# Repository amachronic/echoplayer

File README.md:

# NOTICE

Development has moved to [SourceHut](https://sr.ht/~aidanm/echoplayer).

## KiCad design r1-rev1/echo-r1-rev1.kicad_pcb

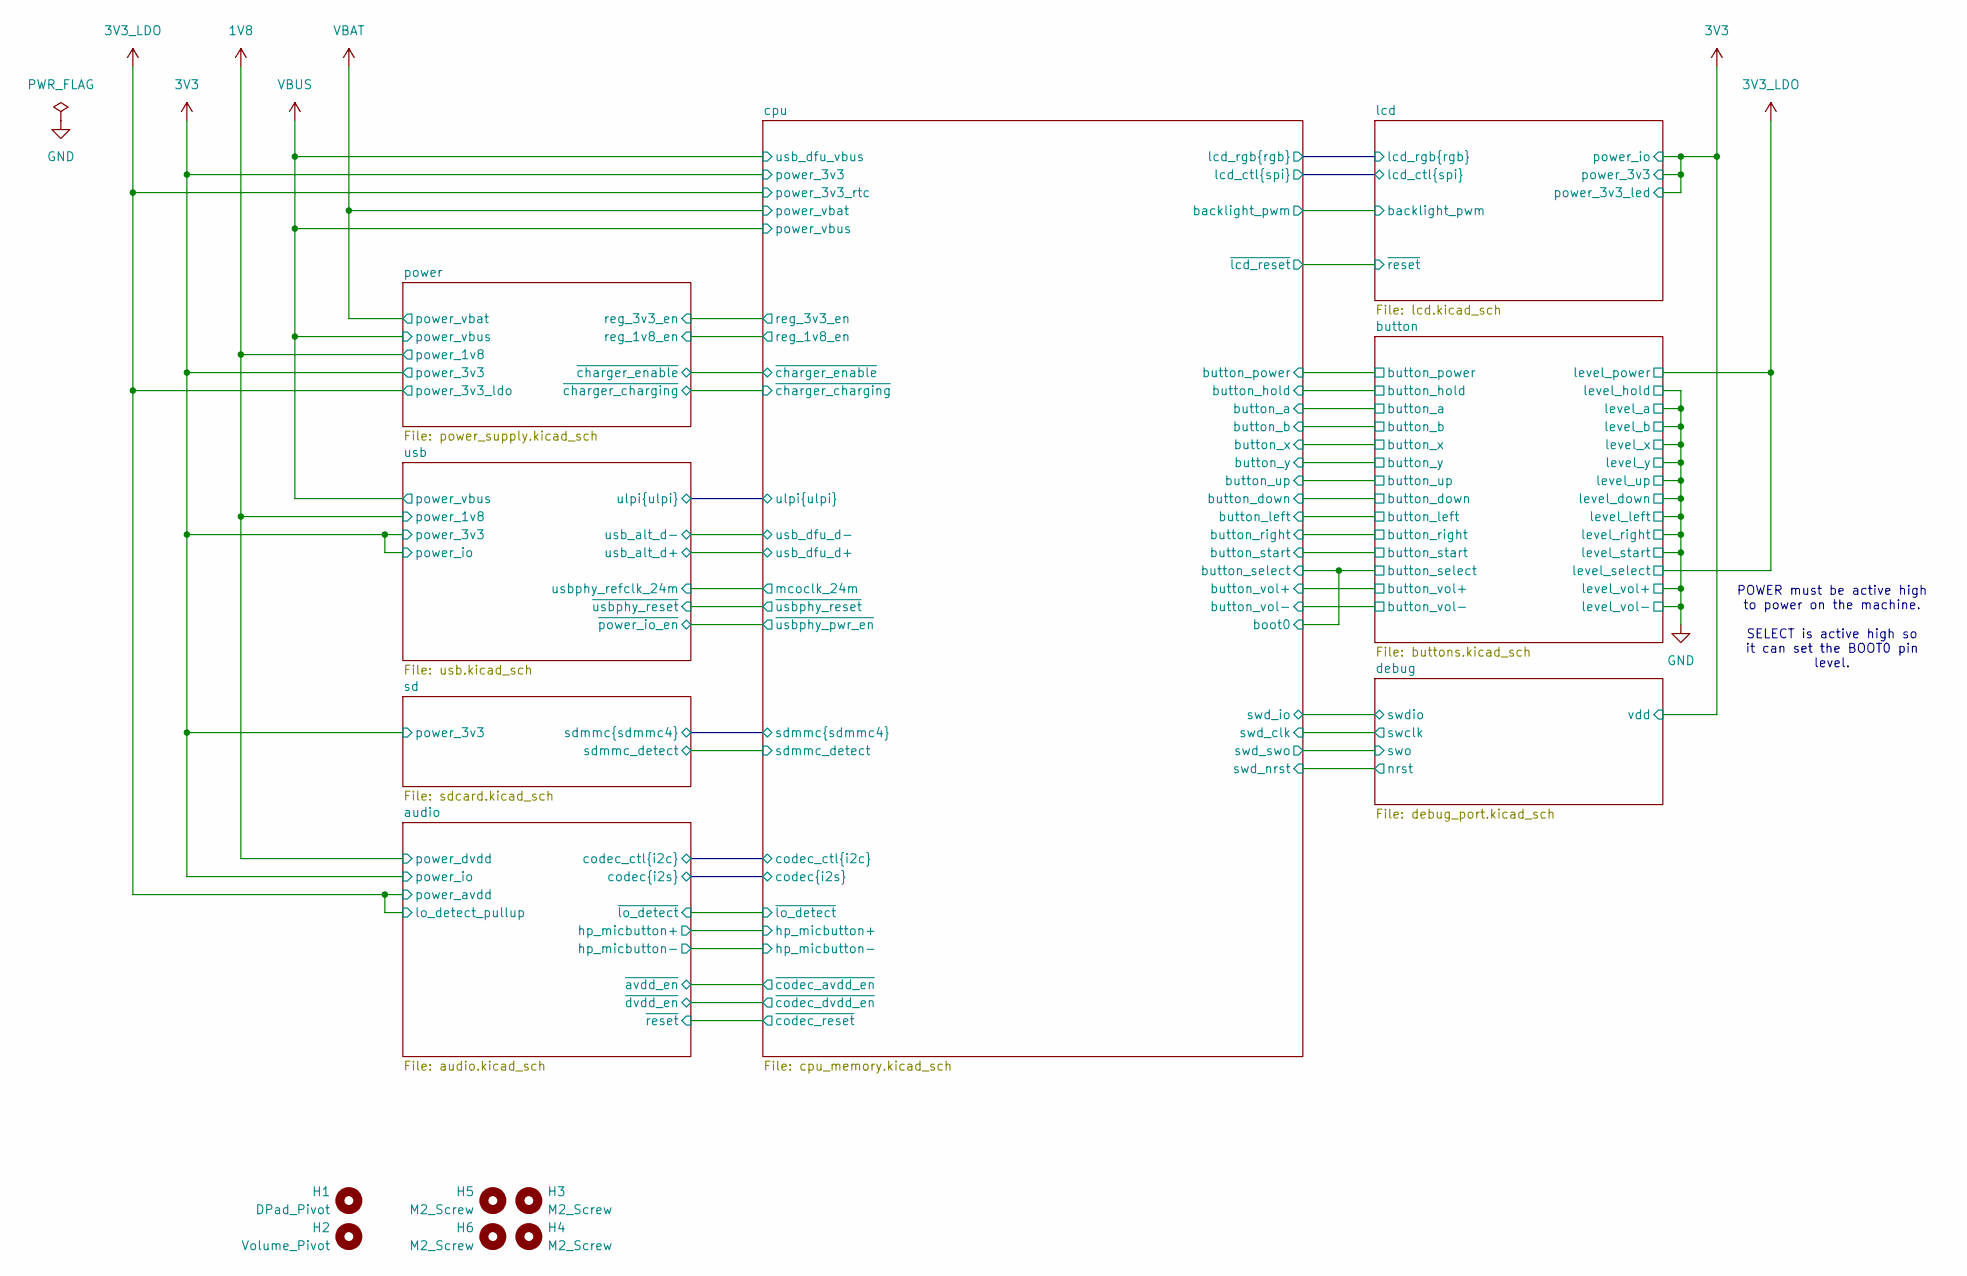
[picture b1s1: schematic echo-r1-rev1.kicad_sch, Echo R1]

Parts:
H1: DPad_Pivot; MountingHole_4mm
H2: Volume_Pivot; MountingHole_4mm
H3, H4, H5, H6: M2_Screw; MountingHole_2.2mm_M2

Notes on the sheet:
POWER must be active high to power on the machine. SELECT is active high so it can set the BOOT0 pin level.

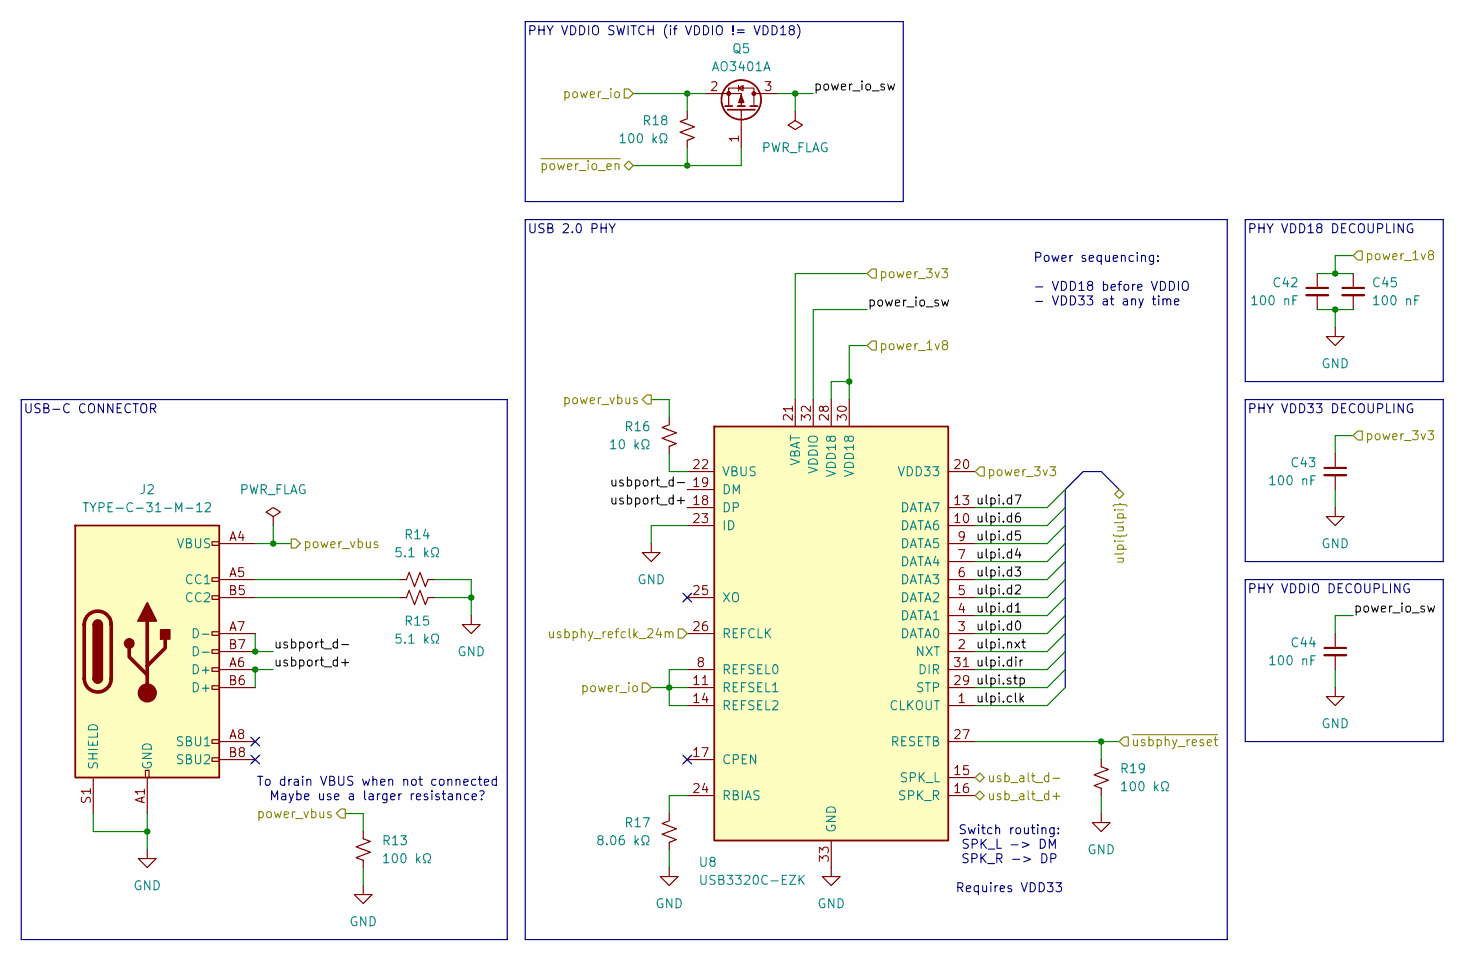
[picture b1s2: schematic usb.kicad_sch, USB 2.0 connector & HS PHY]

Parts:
C42, C43, C44, C45: 100 nF; C_0402_1005Metric; LCSC# C77020
J2: TYPE-C-31-M-12; USB_C-Hroparts-TYPE-C-31-M-12; LCSC# C165948
Q5: AO3401A; SOT-23; LCSC# C347476
R13, R18, R19: 100 kΩ; R_0402_1005Metric; LCSC# C60491
R14, R15: 5.1 kΩ; R_0402_1005Metric; LCSC# C25905
R16: 10 kΩ; R_0402_1005Metric; LCSC# C60490
R17: 8.06 kΩ; R_0402_1005Metric; LCSC# C276278
U8: USB3320C-EZK; QFN-32-1EP_5x5mm_P0.5mm_EP3.1x3.1mm_ThermalVias; LCSC# C132156

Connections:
1V8: C42.1, C45.1, U8.28 (VDD18), U8.30 (VDD18); also elsewhere on the board
3V3: C43.1, Q5.2 (S), R18.1, U8.8 (REFSEL0), U8.11 (REFSEL1), U8.14 (REFSEL2), U8.20 (VDD33), U8.21 (VBAT); also elsewhere on the board
/cpu/mcoclk_24m: U8.26 (REFCLK); also elsewhere on the board
/cpu/ulpi.clk: U8.1 (CLKOUT); also elsewhere on the board
/cpu/ulpi.d0: U8.3 (DATA0); also elsewhere on the board
/cpu/ulpi.d1: U8.4 (DATA1); also elsewhere on the board
/cpu/ulpi.d2: U8.5 (DATA2); also elsewhere on the board
/cpu/ulpi.d3: U8.6 (DATA3); also elsewhere on the board
/cpu/ulpi.d4: U8.7 (DATA4); also elsewhere on the board
/cpu/ulpi.d5: U8.9 (DATA5); also elsewhere on the board
/cpu/ulpi.d6: U8.10 (DATA6); also elsewhere on the board
/cpu/ulpi.d7: U8.13 (DATA7); also elsewhere on the board
/cpu/ulpi.dir: U8.31 (DIR); also elsewhere on the board
/cpu/ulpi.nxt: U8.2 (NXT); also elsewhere on the board
/cpu/ulpi.stp: U8.29 (STP); also elsewhere on the board
/cpu/usb_dfu_d+: U8.16 (SPK_R); also elsewhere on the board
/cpu/usb_dfu_d-: U8.15 (SPK_L); also elsewhere on the board
/cpu/~usbphy_pwr_en: Q5.1 (G), R18.2; also elsewhere on the board
/cpu/~usbphy_reset: R19.1, U8.27 (RESETB); also elsewhere on the board
/usb/power_io_sw: C44.1, Q5.3 (D), U8.32 (VDDIO)
/usb/usbport_d+: J2.A6 (D+), J2.B6 (D+), U8.18 (DP)
/usb/usbport_d-: J2.A7 (D-), J2.B7 (D-), U8.19 (DM)
GND: C42.2, C43.2, C44.2, C45.2, J2.A1 (GND), J2.A12 (GND), J2.B1 (GND), J2.B12 (GND), J2.S1 (SHIELD), R13.2, R14.2, R15.2, R17.1, R19.2, U8.23 (ID), U8.33 (GND); also elsewhere on the board
unnamed: J2.A5 (CC1), R14.1
unnamed: J2.B5 (CC2), R15.1
unnamed: R17.2, U8.24 (RBIAS)
unnamed: R16.1, U8.22 (VBUS)
VBUS: J2.A4 (VBUS), J2.A9 (VBUS), J2.B4 (VBUS), J2.B9 (VBUS), R13.1, R16.2; also elsewhere on the board

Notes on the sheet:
USB 2.0 PHY
Switch routing: SPK_L -> DM SPK_R -> DP Requires VDD33
To drain VBUS when not connected Maybe use a larger resistance?
USB-C CONNECTOR
PHY VDDIO DECOUPLING
PHY VDD33 DECOUPLING
PHY VDD18 DECOUPLING
Power sequencing: - VDD18 before VDDIO - VDD33 at any time
PHY VDDIO SWITCH (if VDDIO != VDD18)

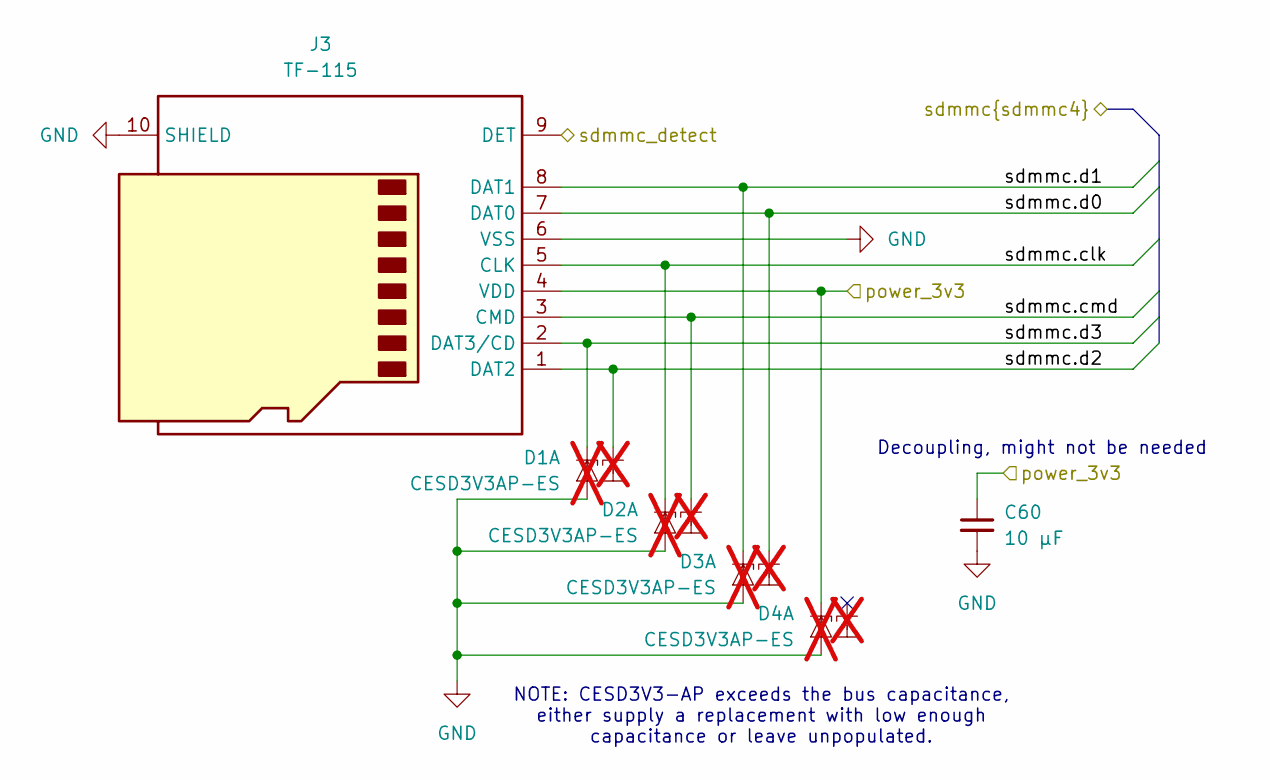
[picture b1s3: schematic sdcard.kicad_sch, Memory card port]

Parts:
C60: 10 µF; C_0603_1608Metric; LCSC# C91606
D1, D2, D3, D4: CESD3V3AP-ES; SOT-23; LCSC# C5199223; not fitted
J3: TF-115; microSD_XUNPU_TF-115; LCSC# C720505

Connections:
3V3: C60.1, D4.1 (K1), J3.4 (VDD); also elsewhere on the board
/cpu/sdmmc.clk: D2.1 (K1), J3.5 (CLK); also elsewhere on the board
/cpu/sdmmc.cmd: D2.2 (K2), J3.3 (CMD); also elsewhere on the board
/cpu/sdmmc.d0: D3.2 (K2), J3.7 (DAT0); also elsewhere on the board
/cpu/sdmmc.d1: D3.1 (K1), J3.8 (DAT1); also elsewhere on the board
/cpu/sdmmc.d2: D1.2 (K2), J3.1 (DAT2); also elsewhere on the board
/cpu/sdmmc.d3: D1.1 (K1), J3.2 (DAT3/CD); also elsewhere on the board
/cpu/sdmmc_detect: J3.9 (DET); also elsewhere on the board
GND: C60.2, D1.3 (A), D2.3 (A), D3.3 (A), D4.3 (A), J3.6 (VSS), J3.10 (SHIELD); also elsewhere on the board

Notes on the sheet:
NOTE: CESD3V3-AP exceeds the bus capacitance, either supply a replacement with low enough capacitance or leave unpopulated.
Decoupling, might not be needed

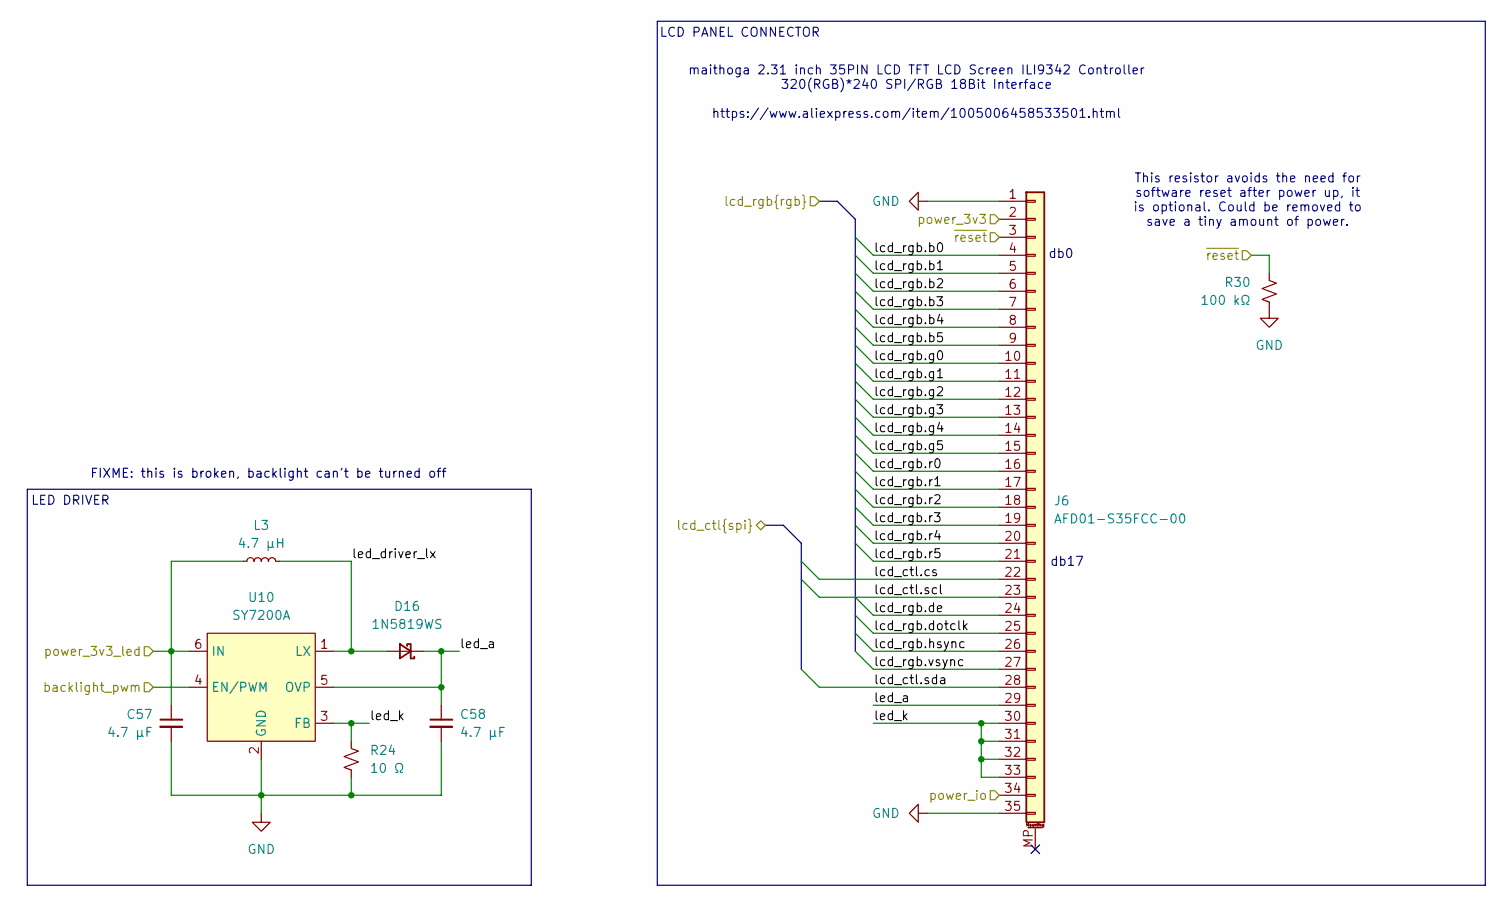
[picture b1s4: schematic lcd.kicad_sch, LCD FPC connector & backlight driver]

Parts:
C57, C58: 4.7 µF; C_0603_1608Metric; LCSC# C69335
D16: 1N5819WS; D_SOD-323; LCSC# C191023
J6: AFD01-S35FCC-00; Conn_Jushuo_AFD01-S35FCC-00_RTL; LCSC# C18198555
L3: 4.7 µH; L_0806_2016Metric; LCSC# C86094
R24: 10 Ω; R_0402_1005Metric; LCSC# C25077
R30: 100 kΩ; R_0402_1005Metric; LCSC# C60491
U10: SY7200A; SOT-23-6; LCSC# C107309

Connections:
3V3: C57.1, J6.2, J6.34, L3.1, U10.6 (IN); also elsewhere on the board
/cpu/backlight_pwm: U10.4 (EN/PWM); also elsewhere on the board
/cpu/lcd_ctl.cs: J6.22; also elsewhere on the board
/cpu/lcd_ctl.scl: J6.23; also elsewhere on the board
/cpu/lcd_ctl.sda: J6.28; also elsewhere on the board
/cpu/lcd_rgb.b0: J6.4; also elsewhere on the board
/cpu/lcd_rgb.b1: J6.5; also elsewhere on the board
/cpu/lcd_rgb.b2: J6.6; also elsewhere on the board
/cpu/lcd_rgb.b3: J6.7; also elsewhere on the board
/cpu/lcd_rgb.b4: J6.8; also elsewhere on the board
/cpu/lcd_rgb.b5: J6.9; also elsewhere on the board
/cpu/lcd_rgb.de: J6.24; also elsewhere on the board
/cpu/lcd_rgb.dotclk: J6.25; also elsewhere on the board
/cpu/lcd_rgb.g0: J6.10; also elsewhere on the board
/cpu/lcd_rgb.g1: J6.11; also elsewhere on the board
/cpu/lcd_rgb.g2: J6.12; also elsewhere on the board
/cpu/lcd_rgb.g3: J6.13; also elsewhere on the board
/cpu/lcd_rgb.g4: J6.14; also elsewhere on the board
/cpu/lcd_rgb.g5: J6.15; also elsewhere on the board
/cpu/lcd_rgb.hsync: J6.26; also elsewhere on the board
/cpu/lcd_rgb.r0: J6.16; also elsewhere on the board
/cpu/lcd_rgb.r1: J6.17; also elsewhere on the board
/cpu/lcd_rgb.r2: J6.18; also elsewhere on the board
/cpu/lcd_rgb.r3: J6.19; also elsewhere on the board
/cpu/lcd_rgb.r4: J6.20; also elsewhere on the board
/cpu/lcd_rgb.r5: J6.21; also elsewhere on the board
/cpu/lcd_rgb.vsync: J6.27; also elsewhere on the board
/cpu/~lcd_reset: J6.3, R30.1; also elsewhere on the board
/lcd/led_a: C58.1, D16.1 (K), J6.29, U10.5 (OVP)
/lcd/led_driver_lx: D16.2 (A), L3.2, U10.1 (LX)
/lcd/led_k: J6.30, J6.31, J6.32, J6.33, R24.1, U10.3 (FB)
GND: C57.2, C58.2, J6.1, J6.35, R24.2, R30.2, U10.2 (GND); also elsewhere on the board

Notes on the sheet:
LCD PANEL CONNECTOR
LED DRIVER
maithoga 2.31 inch 35PIN LCD TFT LCD Screen ILI9342 Controller 320(RGB)*240 SPI/RGB 18Bit Interface https://www.aliexpress.com/item/1005006458533501.html
db0
This resistor avoids the need for software reset after power up, it is optional. Could be removed to save a tiny amount of power.
FIXME: this is broken, backlight can't be turned off
db17

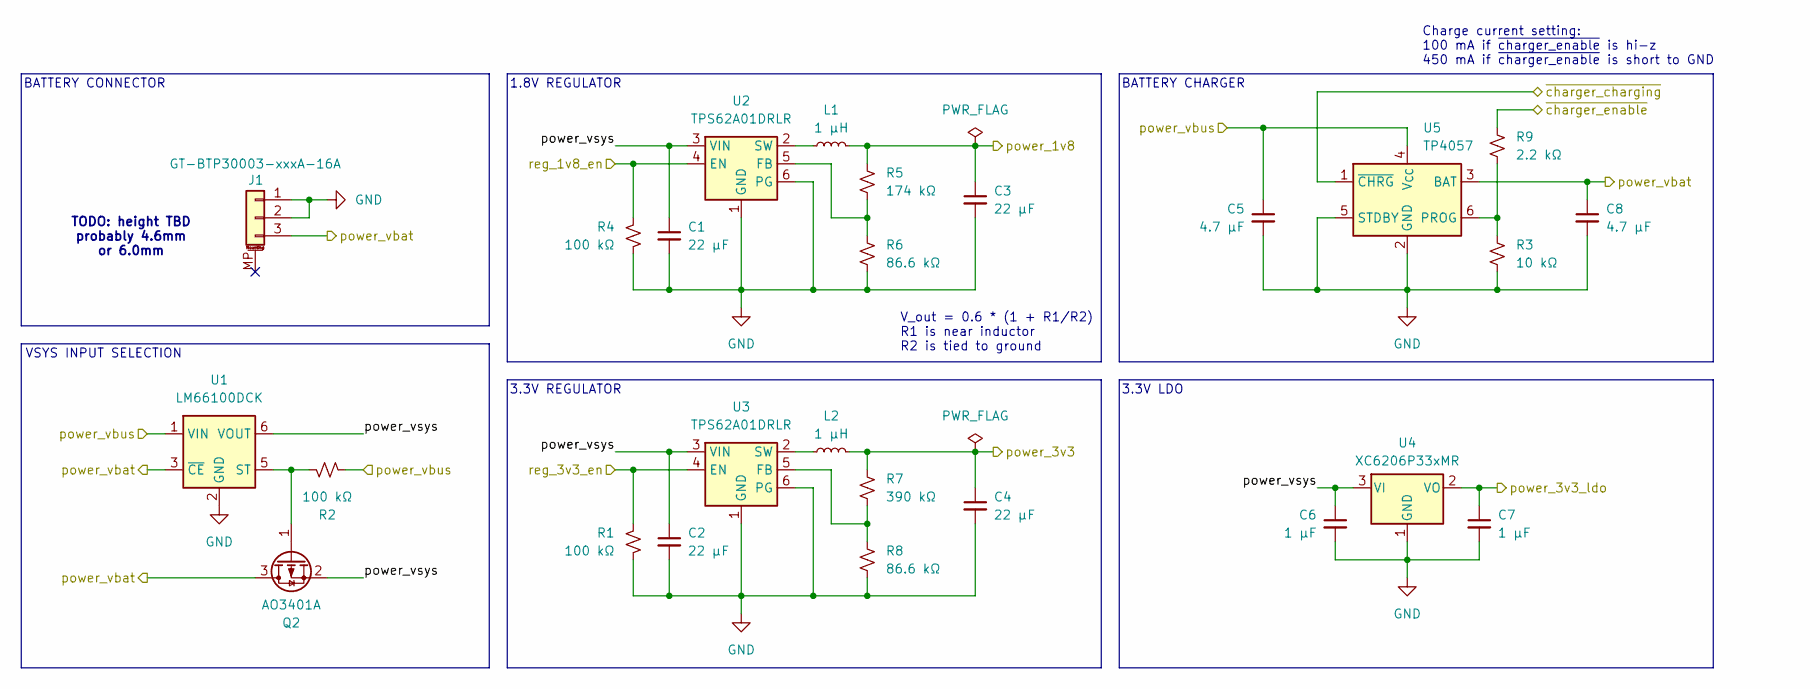
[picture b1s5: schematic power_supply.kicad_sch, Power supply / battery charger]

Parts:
C1, C2, C3, C4: 22 µF; C_0805_2012Metric; LCSC# C86816
C5, C8: 4.7 µF; C_0603_1608Metric; LCSC# C69335
C6, C7: 1 µF; C_0402_1005Metric; LCSC# C52923
J1: GT-BTP30003-xxxA-16A; Conn_GT-BTP30003-xxxxA-016A; LCSC# C41378737
L1, L2: 1 µH; L_0806_2016Metric; LCSC# C161082
Q2: AO3401A; SOT-23; LCSC# C347476
R1, R2, R4: 100 kΩ; R_0402_1005Metric; LCSC# C60491
R3: 10 kΩ; R_0402_1005Metric; LCSC# C60490
R5: 174 kΩ; R_0603_1608Metric; LCSC# C2933159
R6, R8: 86.6 kΩ; R_0603_1608Metric; LCSC# C3000725
R7: 390 kΩ; R_0603_1608Metric; LCSC# C23150
R9: 2.2 kΩ; R_0402_1005Metric; LCSC# C114762
U1: LM66100DCK; Texas_R-PDSO-G6; LCSC# C2869734
U2, U3: TPS62A01DRLR; SOT-563; LCSC# C5157937
U4: XC6206P33xMR; SOT-23-3; LCSC# C5446
U5: TP4057; TSOT-23-6; LCSC# C725791

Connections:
1V8: C3.1, L1.2, R5.1; also elsewhere on the board
3V3: C4.1, L2.2, R7.1; also elsewhere on the board
3V3_LDO: C7.1, U4.2 (VO); also elsewhere on the board
/cpu/reg_1v8_en: R4.1, U2.4 (EN); also elsewhere on the board
/cpu/reg_3v3_en: R1.1, U3.4 (EN); also elsewhere on the board
/cpu/~charger_charging: U5.1 (~CHRG); also elsewhere on the board
/cpu/~charger_enable: R9.1; also elsewhere on the board
/power/power_vsys: C1.1, C2.1, C6.1, Q2.2 (S), U1.6 (VOUT), U2.3 (VIN), U3.3 (VIN), U4.3 (VI)
GND: C1.2, C2.2, C3.2, C4.2, C5.2, C6.2, C7.2, C8.2, J1.1, J1.2, R1.2, R3.2, R4.2, R6.2, R8.2, U1.2 (GND), U2.1 (GND), U2.6 (PG), U3.1 (GND), U3.6 (PG), U4.1 (GND), U5.2 (GND), U5.5 (STDBY); also elsewhere on the board
unnamed: Q2.1 (G), R2.2, U1.5 (ST)
unnamed: R5.2, R6.1, U2.5 (FB)
unnamed: L1.1, U2.2 (SW)
unnamed: R7.2, R8.1, U3.5 (FB)
unnamed: L2.1, U3.2 (SW)
unnamed: R3.1, R9.2, U5.6 (PROG)
VBAT: C8.1, J1.3, Q2.3 (D), U1.3 (~CE), U5.3 (BAT); also elsewhere on the board
VBUS: C5.1, R2.1, U1.1 (VIN), U5.4 (V_{CC}); also elsewhere on the board

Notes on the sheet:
TODO: height TBD probably 4.6mm or 6.0mm
3.3V REGULATOR
V_out = 0.6 * (1 + R1/R2) R1 is near inductor R2 is tied to ground
1.8V REGULATOR
Charge current setting: 100 mA if ~{charger_enable} is hi-z 450 mA if ~{charger_enable} is short to GND
BATTERY CHARGER
BATTERY CONNECTOR
3.3V LDO
VSYS INPUT SELECTION

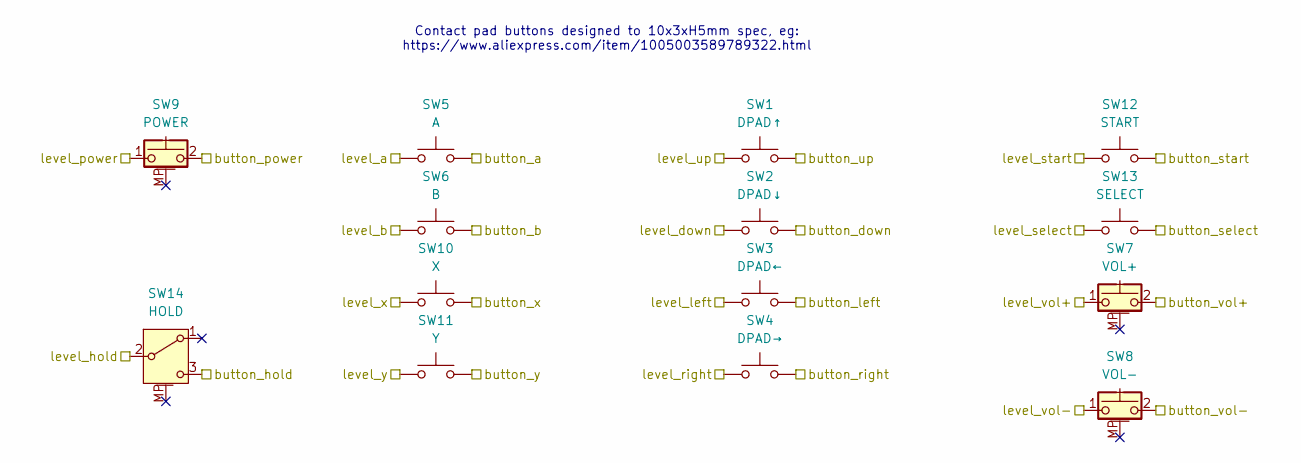
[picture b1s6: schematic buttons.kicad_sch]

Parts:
SW1: DPAD↑; Switch_ContactPad_10x3mm_Cross
SW2: DPAD↓; Switch_ContactPad_10x3mm_Cross
SW3: DPAD←; Switch_ContactPad_10x3mm_Cross
SW4: DPAD→; Switch_ContactPad_10x3mm_Cross
SW5: A; Switch_ContactPad_10x3mm_Cross
SW6: B; Switch_ContactPad_10x3mm_Cross
SW7: VOL+; Switch_XKB_TS-1010-C-A; LCSC# C318941
SW8: VOL-; Switch_XKB_TS-1010-C-A; LCSC# C318941
SW9: POWER; Switch_XKB_TS-1010-C-A; LCSC# C318941
SW10: X; Switch_ContactPad_10x3mm_Cross
SW11: Y; Switch_ContactPad_10x3mm_Cross
SW12: START; Switch_XUNPU_TS-1088-AR; LCSC# C720477
SW13: SELECT; Switch_XUNPU_TS-1088-AR; LCSC# C720477
SW14: HOLD; Switch_SHOUHAN_MSK12C02-HB; LCSC# C431541

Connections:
3V3_LDO: SW9.1, SW13.1; also elsewhere on the board
/button/button_a: SW5.2; also elsewhere on the board
/button/button_b: SW6.2; also elsewhere on the board
/button/button_down: SW2.2; also elsewhere on the board
/button/button_hold: SW14.3 (C); also elsewhere on the board
/button/button_left: SW3.2; also elsewhere on the board
/button/button_power: SW9.2; also elsewhere on the board
/button/button_right: SW4.2; also elsewhere on the board
/button/button_select: SW13.2; also elsewhere on the board
/button/button_start: SW12.2; also elsewhere on the board
/button/button_up: SW1.2; also elsewhere on the board
/button/button_vol+: SW7.2; also elsewhere on the board
/button/button_vol-: SW8.2; also elsewhere on the board
/button/button_x: SW10.2; also elsewhere on the board
/button/button_y: SW11.2; also elsewhere on the board
GND: SW1.1, SW2.1, SW3.1, SW4.1, SW5.1, SW6.1, SW7.1, SW8.1, SW10.1, SW11.1, SW12.1, SW14.2 (B); also elsewhere on the board

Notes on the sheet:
Contact pad buttons designed to 10x3xH5mm spec, eg: https://www.aliexpress.com/item/1005003589789322.html
